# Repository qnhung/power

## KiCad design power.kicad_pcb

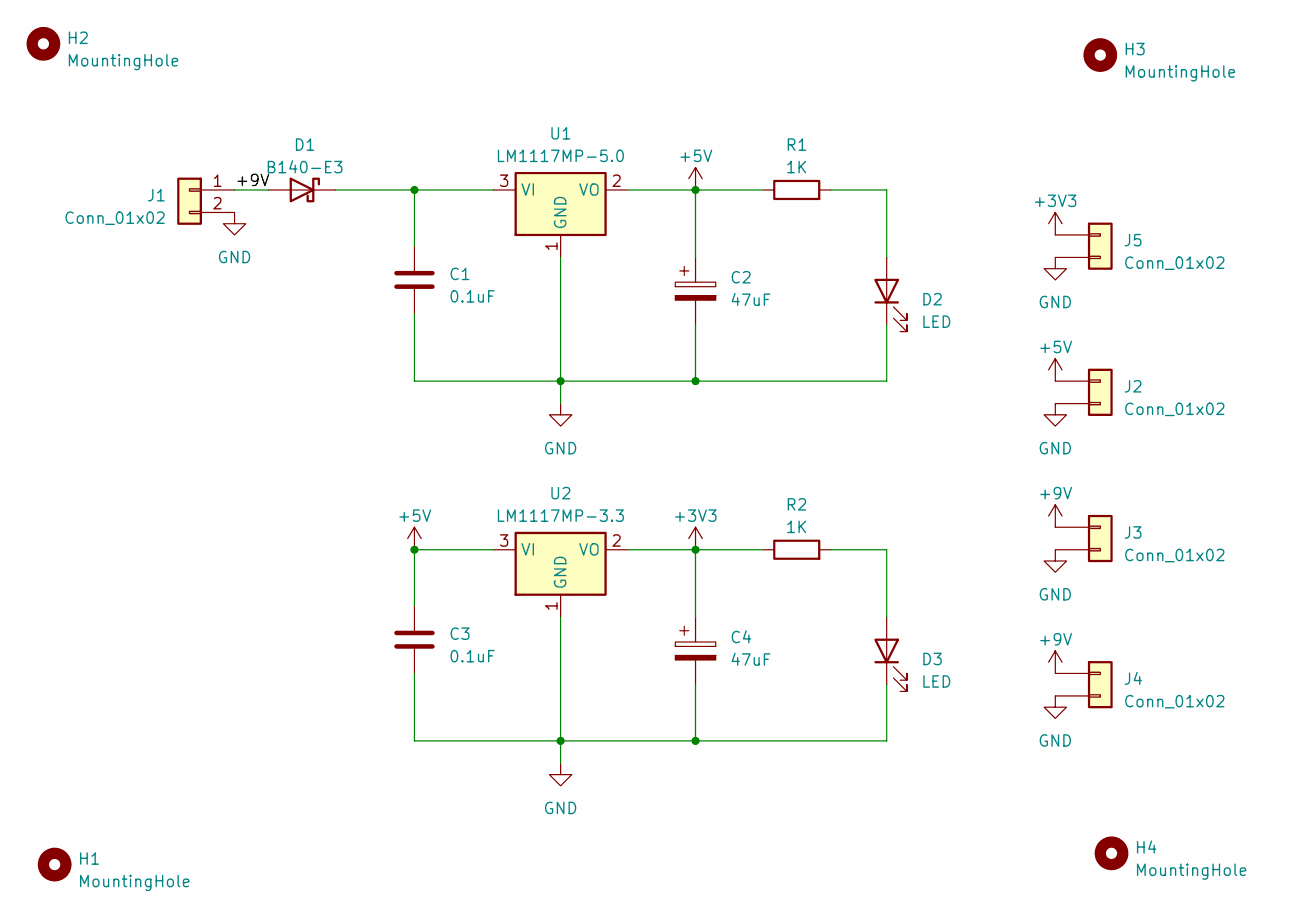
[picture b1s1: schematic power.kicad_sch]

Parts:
C1: 0.1uF; LED_0805_2012Metric_Pad1.15x1.40mm_HandSolder
C2, C4: 47uF; CP_Elec_6.3x5.4
C3: 0.1uF; C_0805_2012Metric_Pad1.18x1.45mm_HandSolder
D1: B140-E3; D_3220_8050Metric_Pad2.65x5.15mm_HandSolder
D2, D3: LED; LED_0805_2012Metric_Pad1.15x1.40mm_HandSolder
H1, H2, H3, H4: MountingHole; MountingHole_3.2mm_M3
J1, J2, J3, J4, J5: Conn_01x02; JST_EH_B2B-EH-A_1x02_P2.50mm_Vertical
R1, R2: 1K; R_0805_2012Metric_Pad1.20x1.40mm_HandSolder
U1: LM1117MP-5.0; SOT-223-3_TabPin2
U2: LM1117MP-3.3; SOT-223-3_TabPin2

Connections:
+3V3: C4.1, J5.1, R2.1, U2.2 (VO)
+5V: C2.1, C3.1, J2.1, R1.1, U1.2 (VO), U2.3 (VI)
+9V: D1.2 (A), J1.1, J3.1, J4.1
GND: C1.2, C2.2, C3.2, C4.2, D2.1 (K), D3.1 (K), J1.2, J2.2, J3.2, J4.2, J5.2, U1.1 (GND), U2.1 (GND)
unnamed: C1.1, D1.1 (K), U1.3 (VI)
unnamed: D2.2 (A), R1.2
unnamed: D3.2 (A), R2.2

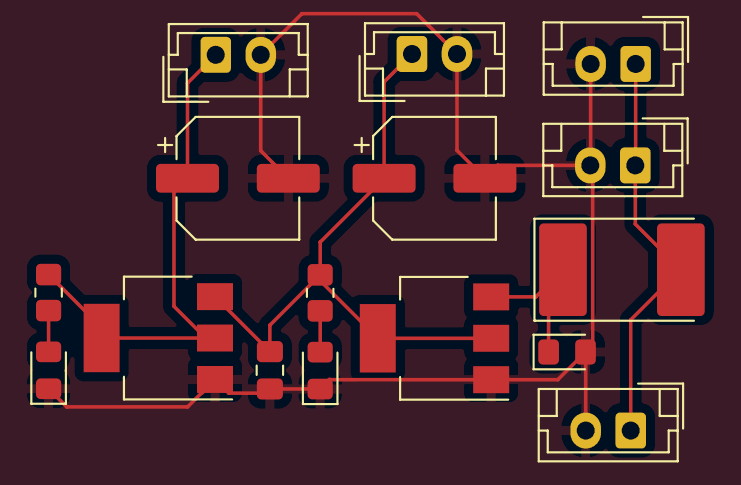
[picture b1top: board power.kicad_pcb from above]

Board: 2 copper layers, 20 parts (0 on the bottom side), 7 nets.
